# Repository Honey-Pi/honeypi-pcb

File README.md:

# HoneyPi-PCB Overview

Printed circuit boards (PCB) for the Raspberry Pi to connect various sensors to avoid the use of jumper cables and flying resistors :-).

Three variants are available (0.x, 2.x, 3.x):
## HoneyPi-PCB V0.1 [link](./PCB_V0.1) no further development or maintenance.

## HoneyPi-PCB V2.x [link](./PCB_V2.x) designed for Raspberry Zero, Zero 2. Read the manual first for Raspberry 3 and 4.  
## HoneyPi-PCB V3.x [link](./PCB_V3.x) designed for Raspberry 3, Raspberry 4 and the Zeros.
## Rasperry 5 is not yet supported.
--> HoneyPi-PCB V2.x and V3.x have a different range of functions.  
 
## Sensor extension board HX711 & DS18b20 for HoneyPi-PCB V2.x [link](./PCB_Sensor_Board_2.x_HX711_DS18b20)  

## Sensor extension board BME280/680 for HoneyPi-PCB V2.x [link](./PCB_Sensor_Board_2.x_BME280_680_ATH10_HDC1080)  
## I2C Extender (one set to extend the range) [link](./PCB_I2C_Extender)

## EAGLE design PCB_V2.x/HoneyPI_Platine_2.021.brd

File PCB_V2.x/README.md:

# HoneyPi-PCB 2.0x

Printed circuit board (PCB) for the Raspberry Pi ZERO to connect various sensors.  
Pitch lenght 2.x mm for Grove plugs or similar.  
Pitch lenght 2.54 mm for terminal blocks as an alternative. 
 
- Three differend possible power supplies possible.  

- 5x HX711...  

- 8x DS18b20 + 1x DS18b20 (TO-92 onboard)  

- 2x BME680 / BME280 

- 1x I²C interface (instead of second BME)

- 1x PCF8591

- incl. interface for the WittyPi / Timer Board

Designed for the Raspian Zero and NOT for Raspian Pi 1 to 4  
Feature list and bill of material is still on working.  
## You can find some helpfull instructions (only in German at the moment ) [here](./Bienenwaage_Platine_2.x_D2.07.pdf)

## V2.0x circuit diagram [link](./Schaltplan_2.021-13-8-2022.pdf)
Check out this [blogpost](https://honey-pi.de/neue-platine-v2-fuer-raspberry-zero/) for the Raspberry Zero.

Status: Tested, working.  
This version has been tested and found to be good and released.

You can upload this [gerber file](./HoneyPI_Platine_2.021_2022-08-13.zip) to [this manufactory service](https://jlcpcb.com/quote) to get few PCBs. 5 pieces of this board cost me about 7 € with delivery. 

### Pictures

Users of the board version 2.01: Please use the schematic 2.01.1 [link](./OLD/Schaltplan_2.01.1-21.01.2021.pdf)

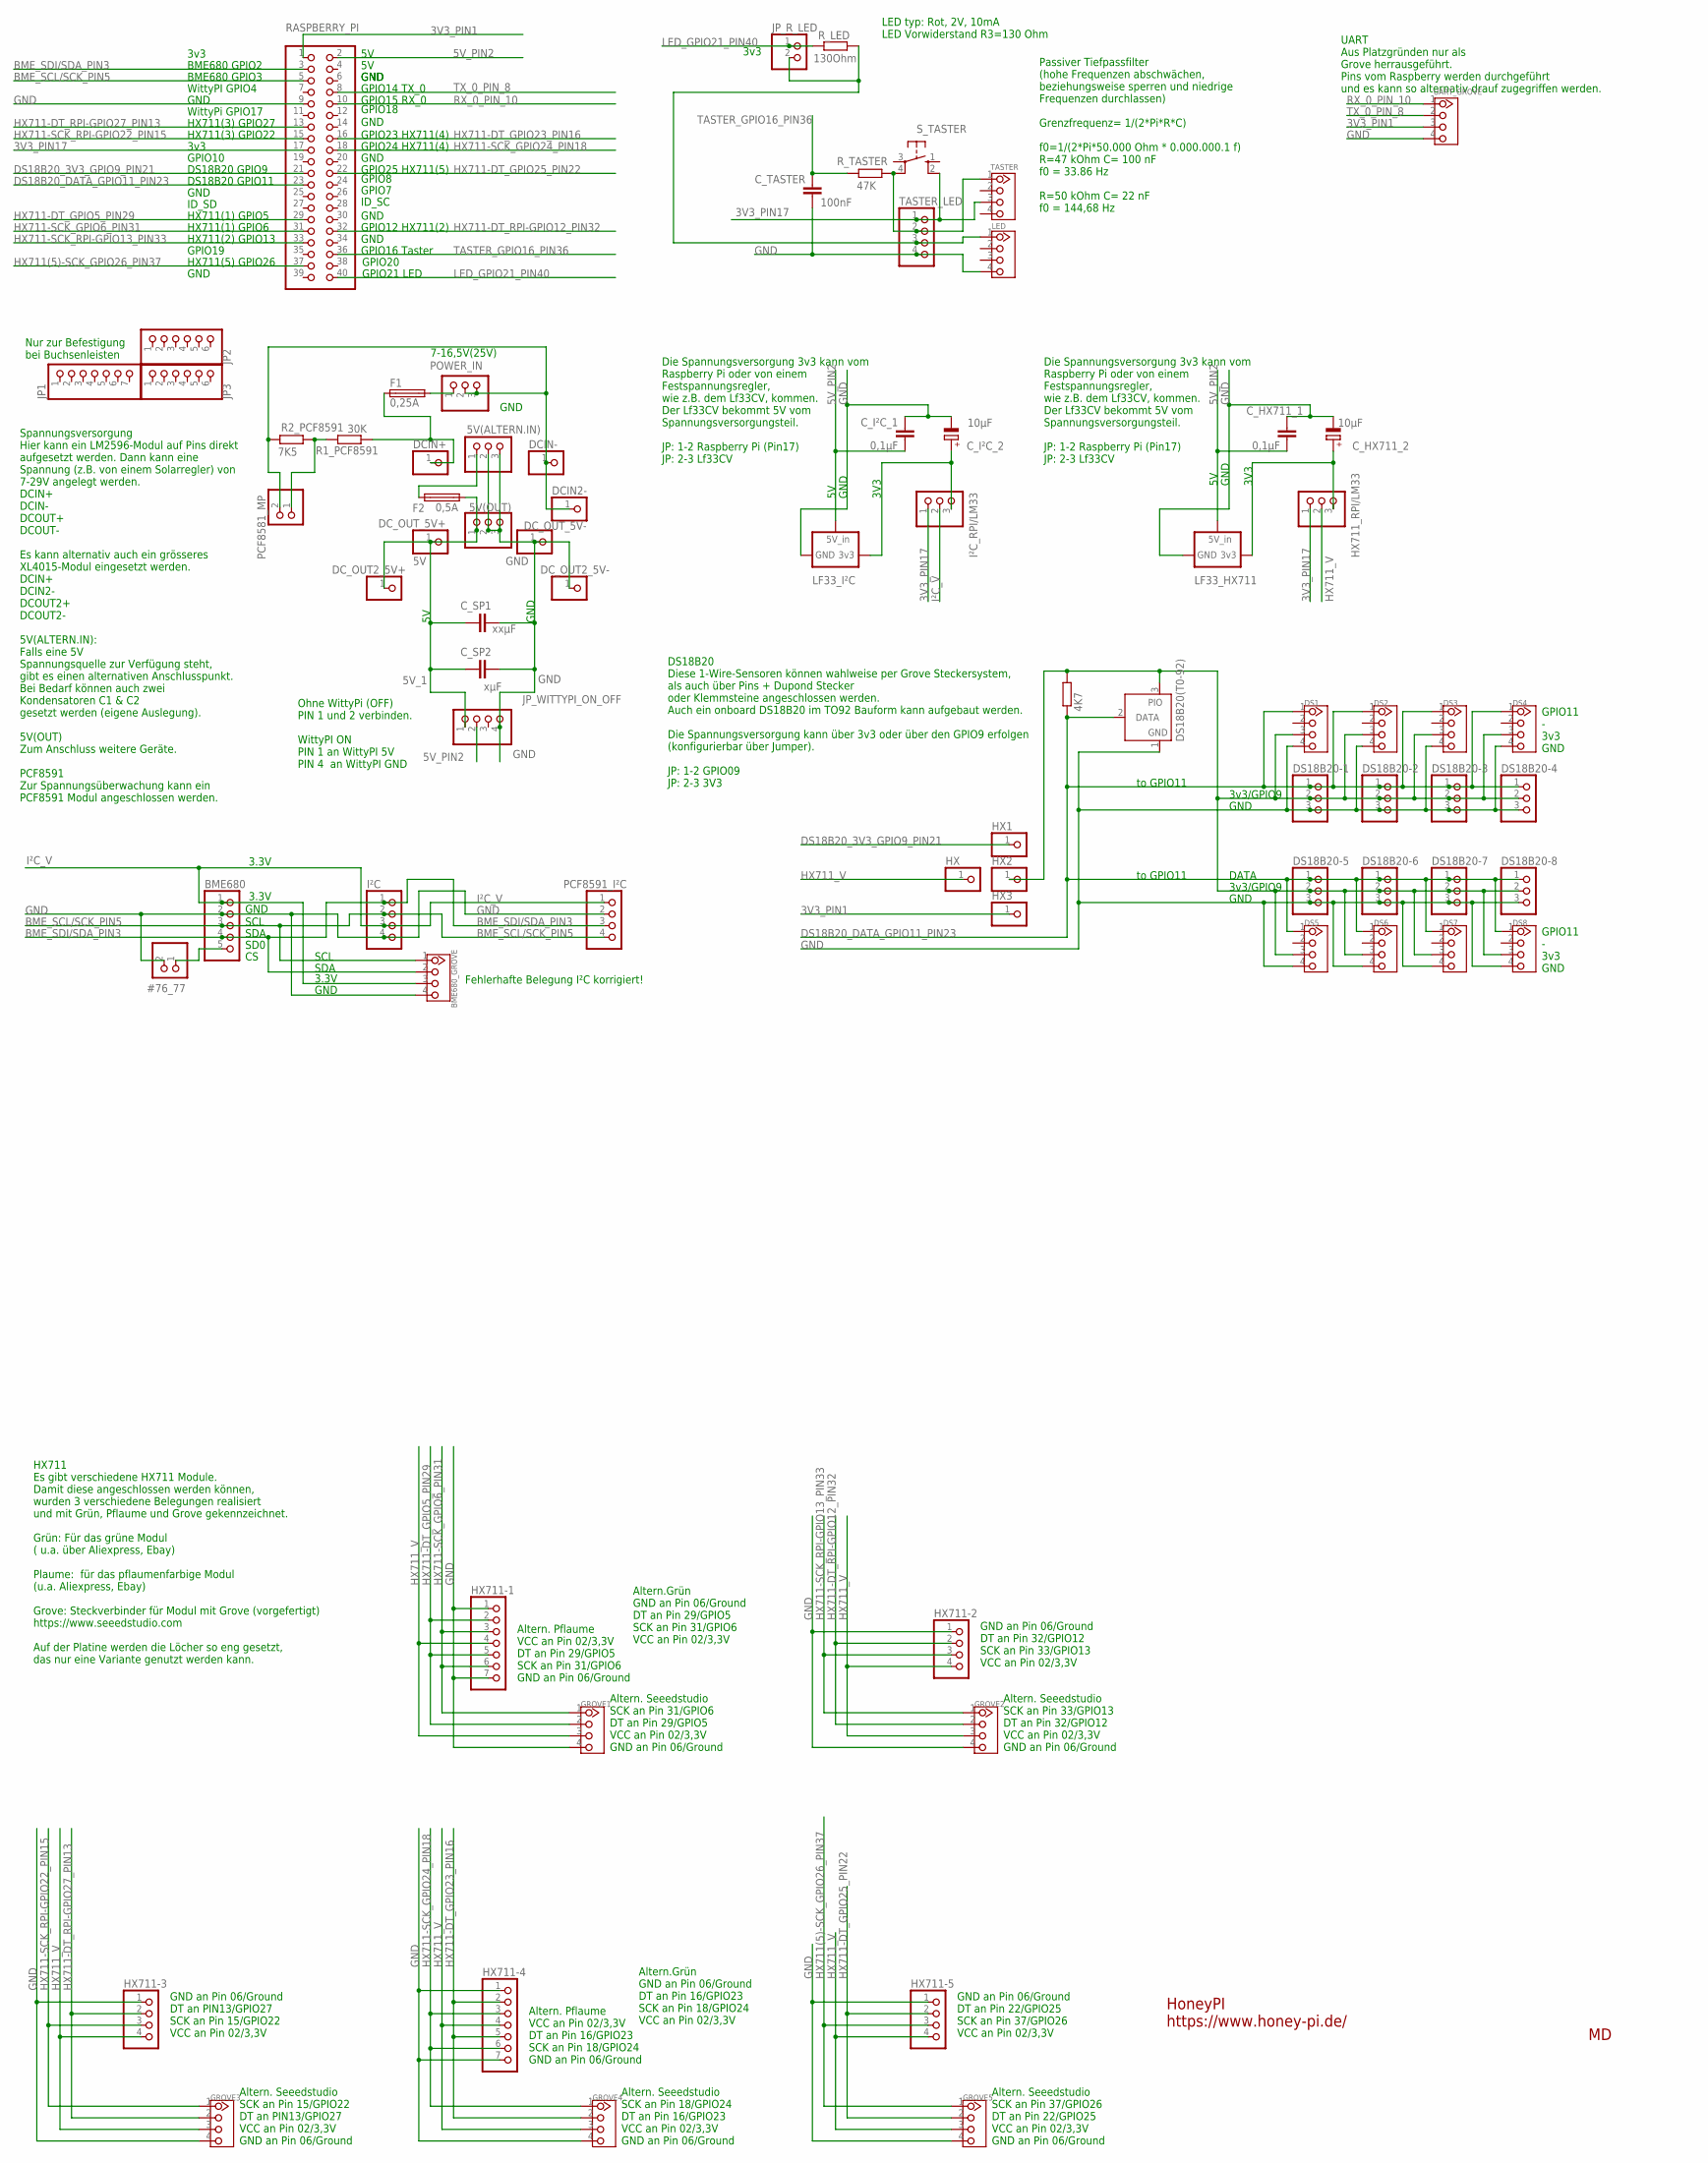
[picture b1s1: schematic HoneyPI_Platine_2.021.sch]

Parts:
5V(ALTERN.IN), 5V(OUT): PINHD-1X3; 1X03
#76_77: PINHD-1X2; 1X02
BME680: PINHD-1X5; 1X05
BME680_GROVE: TWIG-4P-2.0-2.0; 4P-2.0
C_HX711_1: 0,1µF; C2.5-3
C_HX711_2: 10µF; E2-5
C_I²C_1: 0,1µF; C2.5-3
C_I²C_2: 10µF; E2-5
C_SP1: xxµF; C2.5-3
C_SP2: xµF; C2.5-3
C_TASTER: 100nF; C2.5-3
DCIN2-: PINHD-1X1; 1X01
DCIN+: PINHD-1X1; 1X01
DCIN-: PINHD-1X1; 1X01
DC_OUT2_5V+, DC_OUT2_5V-: PINHD-1X1; 1X01
DC_OUT_5V+: 5V; 1X01
DC_OUT_5V-: GND; 1X01
DS1, DS2, DS3, DS4, DS5, DS6, DS7, DS8: TWIG-4P-2.0-2.0; 4P-2.0
DS18B20(T0-92): DS18b20; TO92-
DS18B20-1, DS18B20-2, DS18B20-3, DS18B20-4, DS18B20-5, DS18B20-6, DS18B20-7, DS18B20-8: PINHD-1X3; 1X03
F1: 0,25A; TR5
F2: 0,5A; TR5
GROVE1, GROVE2, GROVE3, GROVE4, GROVE5: TWIG-4P-2.0-2.0; 4P-2.0
HX, HX1, HX2, HX3: PINHD-1X1; 1X01
HX711-1, HX711-4: PINHD-1X7; 1X07
HX711-2, HX711-3, HX711-5: PINHD-1X4; 1X04
HX711_RPI/LM33: PINHD-1X3; 1X03
I²C: PINHD-1X4; 1X04
I²C_RPI/LM33: PINHD-1X3; 1X03
JP1: PINHD-1X7; 1X07
JP2, JP3: PINHD-1X6; 1X06
JP_R_LED: PINHD-1X2; 1X02
JP_WITTYPI_ON_OFF: PINHD-1X4; 1X04
LED: TWIG-4P-2.0-2.0; 4P-2.0
LF33_HX711, LF33_I²C: LM33CV; 337TS
PCF8581_MP: PINHD-1X2; 1X02
PCF8591_I²C: PINHD-1X4; 1X04
POWER_IN: PINHD-1X3; 1X03
R1_PCF8591: 30K; 0204/7
R2_PCF8591: 7K5; 0204/7
RASPBERRY_PI: PINHD-2X20; 2X20
R_DS18B20: 4K7; 0204/7
R_LED: 130Ohm; 0204/7
R_TASTER: 47K; 0204/7
S_TASTER: 10-XX; B3F-10XX
TASTER: TWIG-4P-2.0-2.0; 4P-2.0
TASTER_LED: PINHD-1X4; 1X04
UART_GROVE: TWIG-4P-2.0-2.0; 4P-2.0

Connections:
3V3: DS1.3, DS2.3, DS3.3, DS4.3, DS5.3, DS6.3, DS7.3, DS8.3, DS18B20(T0-92).3 (PIO), DS18B20-1.2, DS18B20-2.2, DS18B20-3.2, DS18B20-4.2, DS18B20-5.2, DS18B20-6.2, DS18B20-7.2, DS18B20-8.2, HX2.1, R_DS18B20.2
3V3_PIN1: HX3.1, RASPBERRY_PI.1, UART_GROVE.3
3V3_PIN17: HX711_RPI/LM33.1, I²C_RPI/LM33.1, RASPBERRY_PI.17, S_TASTER.2 (S1), TASTER.3, TASTER_LED.1
5V_1: 5V(OUT).1, C_SP1.1, C_SP2.1, DC_OUT2_5V+.1, DC_OUT_5V+.1, F2.1, JP_WITTYPI_ON_OFF.1
5V_PIN2: C_HX711_1.1, C_I²C_1.1, JP_WITTYPI_ON_OFF.2, LF33_HX711.1 (5V), LF33_I²C.1 (5V), RASPBERRY_PI.2
BME_SCL/SCK_PIN5: BME680.3, BME680_GROVE.1, I²C.2, PCF8591_I²C.4, RASPBERRY_PI.5
BME_SDI/SDA_PIN3: BME680.4, BME680_GROVE.2, I²C.1, PCF8591_I²C.3, RASPBERRY_PI.3
DS18B20_3V3_GPIO9_PIN21: HX1.1, RASPBERRY_PI.21
DS18B20_DATA_GPIO11_PIN23: DS1.1, DS2.1, DS3.1, DS4.1, DS5.1, DS6.1, DS7.1, DS8.1, DS18B20(T0-92).2 (DATA), DS18B20-1.1, DS18B20-2.1, DS18B20-3.1, DS18B20-4.1, DS18B20-5.1, DS18B20-6.1, DS18B20-7.1, DS18B20-8.1, RASPBERRY_PI.23, R_DS18B20.1
GND: 5V(ALTERN.IN).2, 5V(ALTERN.IN).3, 5V(OUT).2, 5V(OUT).3, #76_77.2, BME680.2, BME680_GROVE.4, C_HX711_1.2, C_HX711_2.-, C_I²C_1.2, C_I²C_2.-, C_SP1.2, C_SP2.2, C_TASTER.1, DC_OUT2_5V-.1, DC_OUT_5V-.1, DS1.4, DS2.4, DS3.4, DS4.4, DS5.4, DS6.4, DS7.4, DS8.4, DS18B20(T0-92).1 (GND), DS18B20-1.3, DS18B20-2.3, DS18B20-3.3, DS18B20-4.3, DS18B20-5.3, DS18B20-6.3, DS18B20-7.3, DS18B20-8.3, GROVE1.4, GROVE2.4, GROVE3.4, GROVE4.4, GROVE5.4, HX711-1.1, HX711-1.7, HX711-2.1, HX711-3.1, HX711-4.1, HX711-4.7, HX711-5.1, I²C.4, JP_WITTYPI_ON_OFF.4, LED.4, LF33_HX711.2 (GND), LF33_I²C.2 (GND), PCF8591_I²C.2, RASPBERRY_PI.9, TASTER_LED.4, UART_GROVE.4
GND20V: DCIN2-.1, DCIN-.1, PCF8581_MP.2, POWER_IN.2, POWER_IN.3, R2_PCF8591.2
HX711(5)-SCK_GPIO26_PIN37: GROVE5.1, HX711-5.3, RASPBERRY_PI.37
HX711-DT_GPIO5_PIN29: GROVE1.2, HX711-1.2, HX711-1.5, RASPBERRY_PI.29
HX711-DT_GPIO23_PIN16: GROVE4.2, HX711-4.2, HX711-4.5, RASPBERRY_PI.16
HX711-DT_GPIO25_PIN22: GROVE5.2, HX711-5.2, RASPBERRY_PI.22
HX711-DT_RPI-GPIO12_PIN32: GROVE2.2, HX711-2.2, RASPBERRY_PI.32
HX711-DT_RPI-GPIO27_PIN13: GROVE3.2, HX711-3.2, RASPBERRY_PI.13
HX711-SCK_GPIO6_PIN31: GROVE1.1, HX711-1.3, HX711-1.6, RASPBERRY_PI.31
HX711-SCK_GPIO24_PIN18: GROVE4.1, HX711-4.3, HX711-4.6, RASPBERRY_PI.18
HX711-SCK_RPI-GPIO13_PIN33: GROVE2.1, HX711-2.3, RASPBERRY_PI.33
HX711-SCK_RPI-GPIO22_PIN15: GROVE3.1, HX711-3.3, RASPBERRY_PI.15
HX711_V: GROVE1.3, GROVE2.3, GROVE3.3, GROVE4.3, GROVE5.3, HX.1, HX711-1.4, HX711-2.4, HX711-3.4, HX711-4.4, HX711-5.4, HX711_RPI/LM33.2
I²C_V: BME680.1, BME680_GROVE.3, I²C.3, I²C_RPI/LM33.2, PCF8591_I²C.1
LED_2: JP_R_LED.2, LED.1, R_LED.2, TASTER_LED.3
LED_GPIO21_PIN40: JP_R_LED.1, RASPBERRY_PI.40, R_LED.1
unnamed: C_I²C_2.+, I²C_RPI/LM33.3, LF33_I²C.3 (OUT3V3)
unnamed: R_TASTER.1, S_TASTER.4 (P1), TASTER.1, TASTER_LED.2
unnamed: C_HX711_2.+, HX711_RPI/LM33.3, LF33_HX711.3 (OUT3V3)
unnamed: #76_77.1, BME680.5
unnamed: 5V(ALTERN.IN).1, F2.2
RX_0_PIN_10: RASPBERRY_PI.10, UART_GROVE.1
SPANNUNGSTEILER1: PCF8581_MP.1, R1_PCF8591.2, R2_PCF8591.1
TASTER_GPIO16_PIN36: C_TASTER.2, RASPBERRY_PI.36, R_TASTER.2
TX_0_PIN_8: RASPBERRY_PI.8, UART_GROVE.2
VDD20V1: DCIN+.1, F1.1, R1_PCF8591.1
VDD20V2: F1.2, POWER_IN.1

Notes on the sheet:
3v3
3v3/GPIO9
DATA
GND
SCL
SDA
SD0
7-16,5V(25V)
Altern. Pflaume VCC an Pin 02/3,3V DT an Pin 29/GPIO5 SCK an Pin 31/GPIO6 GND an Pin 06/Ground
GPIO18
Altern.Grün GND an Pin 06/Ground DT an Pin 29/GPIO5 SCK an Pin 31/GPIO6 VCC an Pin 02/3,3V
BME680 GPIO2
BME680 GPIO3
WittyPI GPIO4
WittyPi GPIO17
DS18B20 GPIO9
DS18B20 GPIO11
HX711(1) GPIO5
HX711(1) GPIO6
HX711(2) GPIO13
GPIO16 Taster
GPIO21 LED
GPIO12 HX711(2)
to GPIO11
GPIO11 - 3v3 GND
GPIO23 HX711(4)
GPIO24 HX711(4)
GPIO25 HX711(5)
HX711(5) GPIO26
GPIO15 RX_0
GPIO14 TX_0
HX711(3) GPIO27
HX711(3) GPIO22
Altern. Seeedstudio SCK an Pin 31/GPIO6 DT an Pin 29/GPIO5 VCC an Pin 02/3,3V GND an Pin 06/Ground
GND an Pin 06/Ground DT an Pin 32/GPIO12 SCK an Pin 33/GPIO13 VCC an Pin 02/3,3V
Altern. Seeedstudio SCK an Pin 33/GPIO13 DT an Pin 32/GPIO12 VCC an Pin 02/3,3V GND an Pin 06/Ground
GND an Pin 06/Ground DT an PIN13/GPIO27 SCK an Pin 15/GPIO22 VCC an Pin 02/3,3V
Altern. Seeedstudio SCK an Pin 15/GPIO22 DT an PIN13/GPIO27 VCC an Pin 02/3,3V GND an Pin 06/Ground
Altern. Pflaume VCC an Pin 02/3,3V DT an Pin 16/GPIO23 SCK an Pin 18/GPIO24 GND an Pin 06/Ground
Altern.Grün GND an Pin 06/Ground DT an Pin 16/GPIO23 SCK an Pin 18/GPIO24 VCC an Pin 02/3,3V

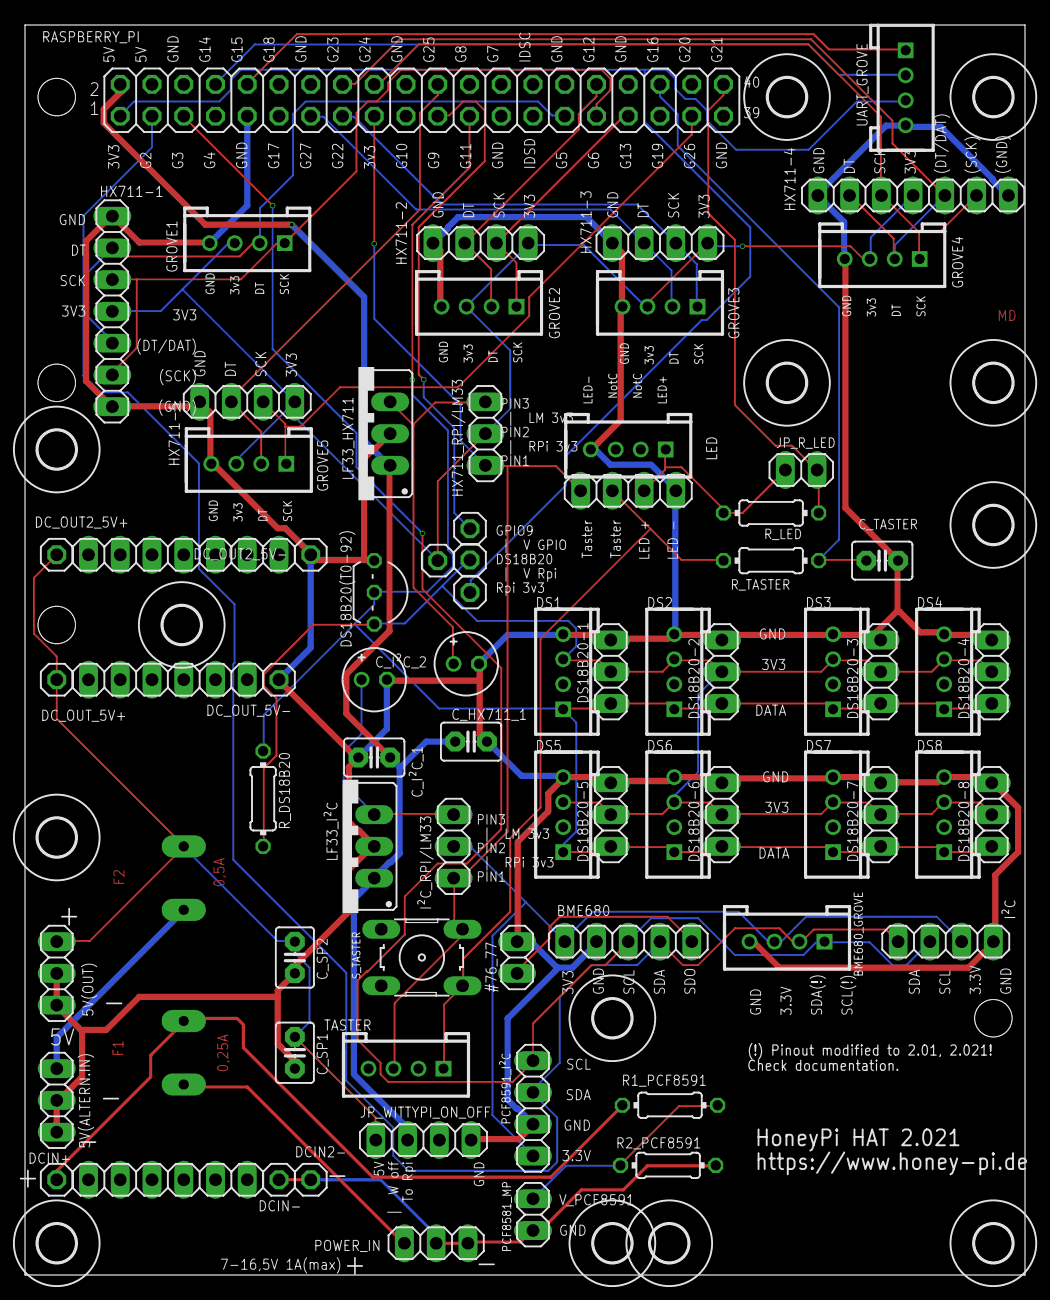
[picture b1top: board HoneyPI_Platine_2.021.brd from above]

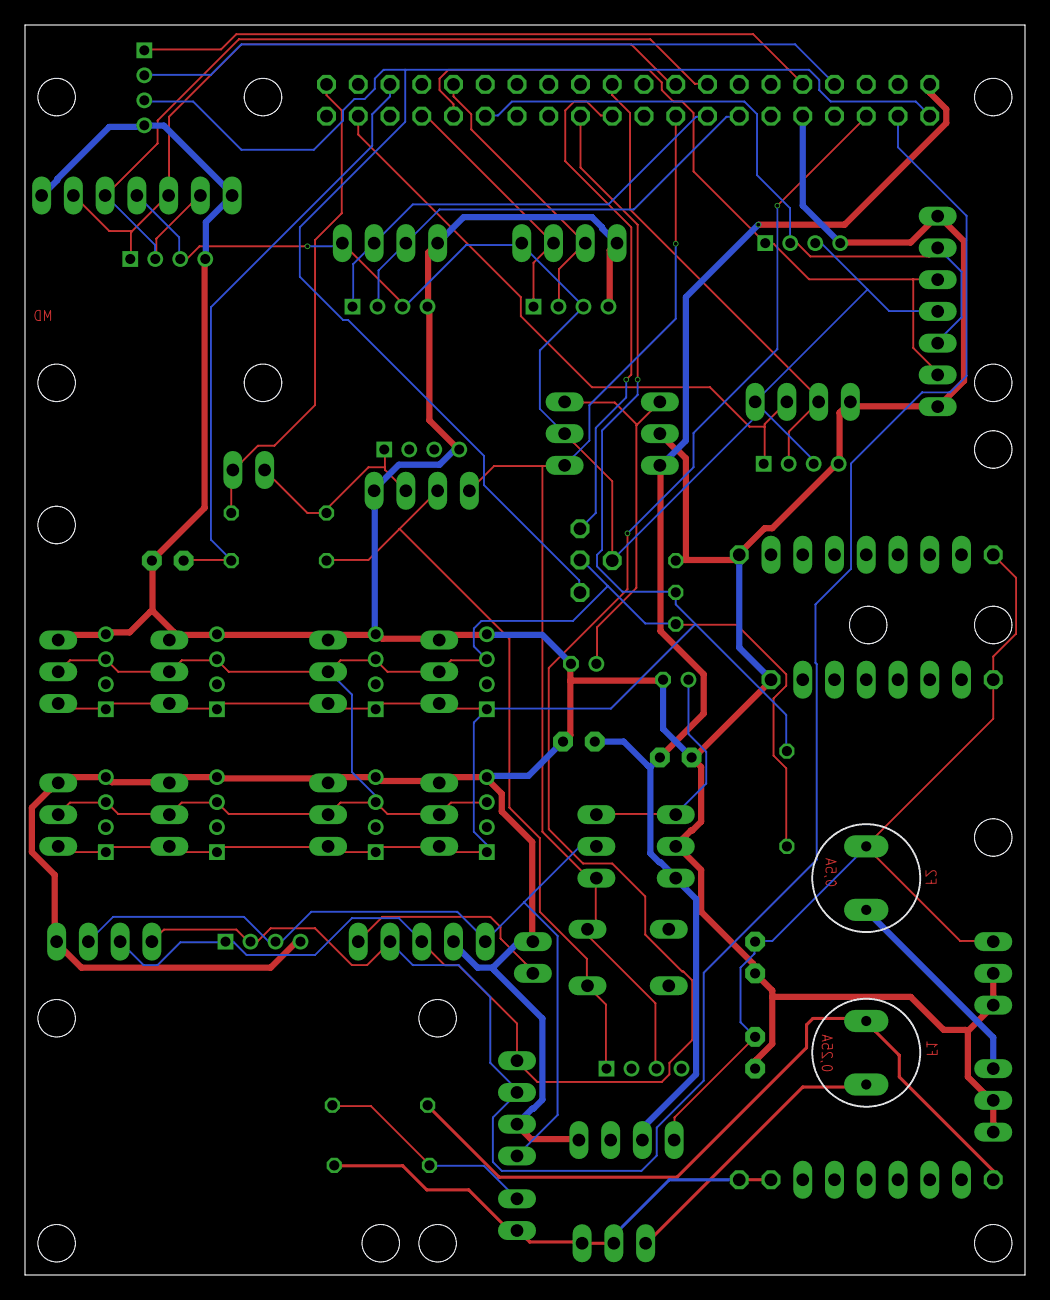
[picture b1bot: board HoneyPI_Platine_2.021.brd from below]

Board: 2 copper layers, 80.0 x 100.0 mm, 89 parts (2 on the bottom side), 36 nets.

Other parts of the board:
U$1, U$2, U$3, U$4, U$5, U$6, U$7, U$8, U$9, U$10, U$11, U$12, U$13: 3,0

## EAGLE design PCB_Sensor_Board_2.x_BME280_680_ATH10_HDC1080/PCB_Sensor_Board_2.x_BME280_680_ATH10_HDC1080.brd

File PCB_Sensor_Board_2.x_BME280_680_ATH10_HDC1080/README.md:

# HoneyPI-PCB Sensor Board 2.x BME280/BME680

Extension board for the HoneyPi-PCB 2.x.  
Pitch lenght 2.0 mm for Grove plugs or similar.  
Pitch lenght 2.54 mm for pins or...  
Designed to be mounted in a separate housing that allows humidity to be measured.  
1x BME680 or BME280 or 1x ATH10 or 1x HDC1080 or 1x sht31
--> We adapt these sensors because of the fixed i2c adresses. 

Feature list and bill of material is still on working.   

## V2.0x circuit diagram [link](./PCB_Sensor_Board_2.x_BME280_680_ATH10_HDC1080.pdf)
Check out this [blogpost](https://www.honey-pi.de/)

Status: Under development.  
This version is currently being procured and tested.  
Please do not order these without having contacted us before.  
Thank you for your understanding!  

You can upload this [gerber file](./PCB_Sensor_Board_2.x_BME280_680_ATH10_HDC1080.zip) to [this manufactory service](https://jlcpcb.com/quote) to get few PCBs. 10 pieces of this board cost about 7 € with delivery. 

### Pictures

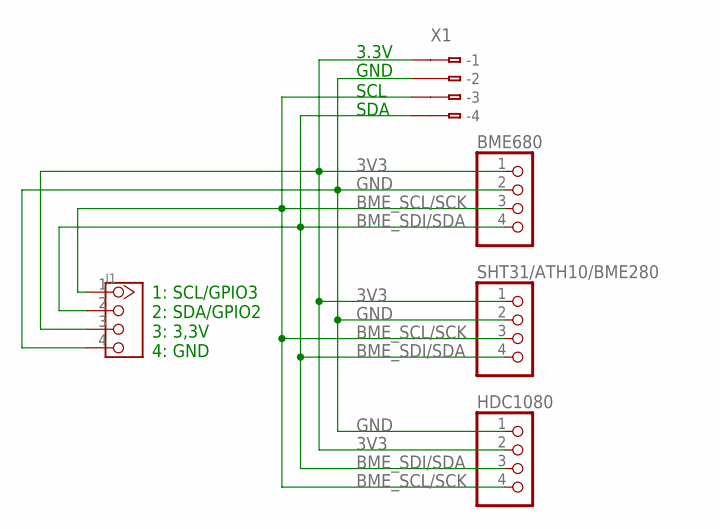
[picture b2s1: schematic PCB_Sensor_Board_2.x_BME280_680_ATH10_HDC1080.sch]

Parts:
BME680: PINHD-1X4; 1X04
HDC1080: PINHD-1X4; 1X04
J1: TWIG-4P-2.0-2.0; 4P-2.0
SHT31/ATH10/BME280: PINHD-1X4; 1X04
X1: 233-504

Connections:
3V3: BME680.1, HDC1080.2, J1.3, SHT31/ATH10/BME280.1, X1.B1 (B-1)
BME_SCL/SCK: BME680.3, HDC1080.4, J1.1, SHT31/ATH10/BME280.3, X1.B3 (B-3)
BME_SDI/SDA: BME680.4, HDC1080.3, J1.2, SHT31/ATH10/BME280.4, X1.B4 (B-4)
GND: BME680.2, HDC1080.1, J1.4, SHT31/ATH10/BME280.2, X1.B2 (B-2)

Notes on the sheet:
GND
SDA
SCL
3.3V
1: SCL/GPIO3 2: SDA/GPIO2 3: 3,3V 4: GND

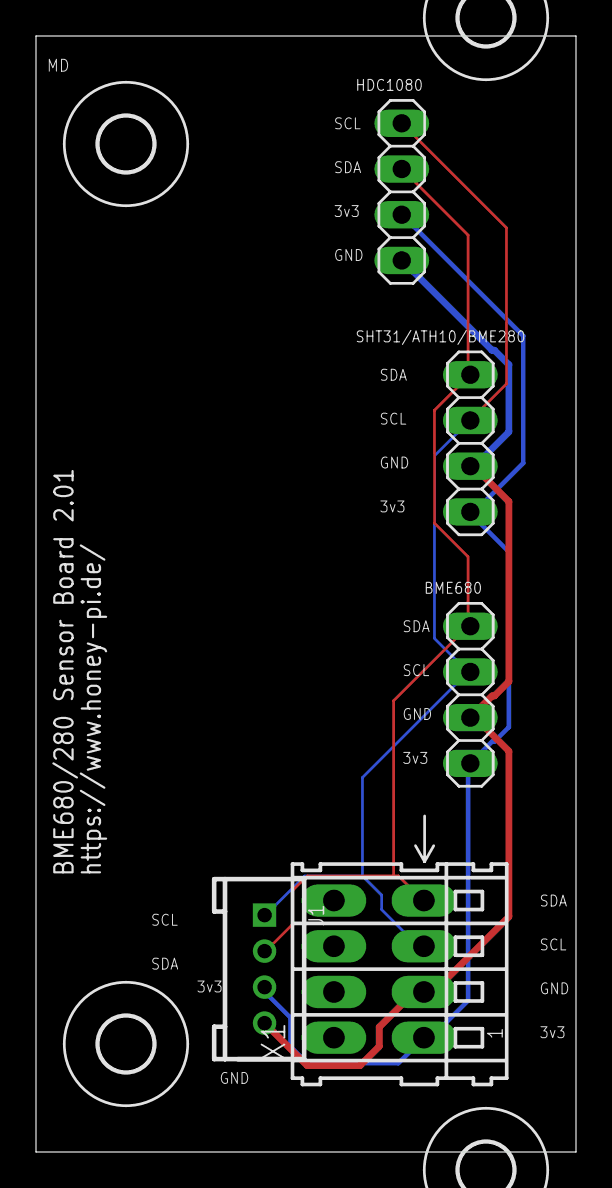
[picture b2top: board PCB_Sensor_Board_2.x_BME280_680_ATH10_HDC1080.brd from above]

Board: 2 copper layers, 30.0 x 62.0 mm, 9 parts (0 on the bottom side), 4 nets.

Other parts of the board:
U$1, U$2, U$3, U$4: 3,0

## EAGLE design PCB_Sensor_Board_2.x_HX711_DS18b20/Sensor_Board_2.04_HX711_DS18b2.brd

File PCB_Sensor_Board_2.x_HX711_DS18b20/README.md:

# HoneyPi-PCB Sensor Board HX711 and DS18b20

Extension board for the HoneyPi-PCB 2.x.   
Pitch lenght 2.0 mm for Grove plugs or similar.  
Pitch lenght 2.54 mm for (e.g.) terminal blocks as an alternative. 
New: Wago cage clamp block support

Designed to be mounted close to the load cell. To ensure that the analogue voltage signal is subject to the least interference.  
Shielded cable to the load cell and aluminium housing are designed for this purpose.  
1x HX711 (two different types)  
3x DS18b20 (cable/external) + 1x DS18b20 TO-92 (board)  

Feature list and bill of material is still on working. 

## V2.0x circuit diagram [link](./HoneyPI_Platine_2.05_Sensor_Plan.pdf)  
Check out this [blogpost](https://www.honey-pi.de/)  

Status: Under development.  
This version is currently being procured and tested.  
Please do not order these without having contacted us before.  
Thank you for your understanding!   

You can upload this [gerber file](./Sensor_Board_2.05_HX711_DS18b2.zip) to [this manufactory service](https://jlcpcb.com/quote) to get few PCBs. 10 pieces of this board cost about 7 € with delivery.  
(price date 2021)

### Pictures

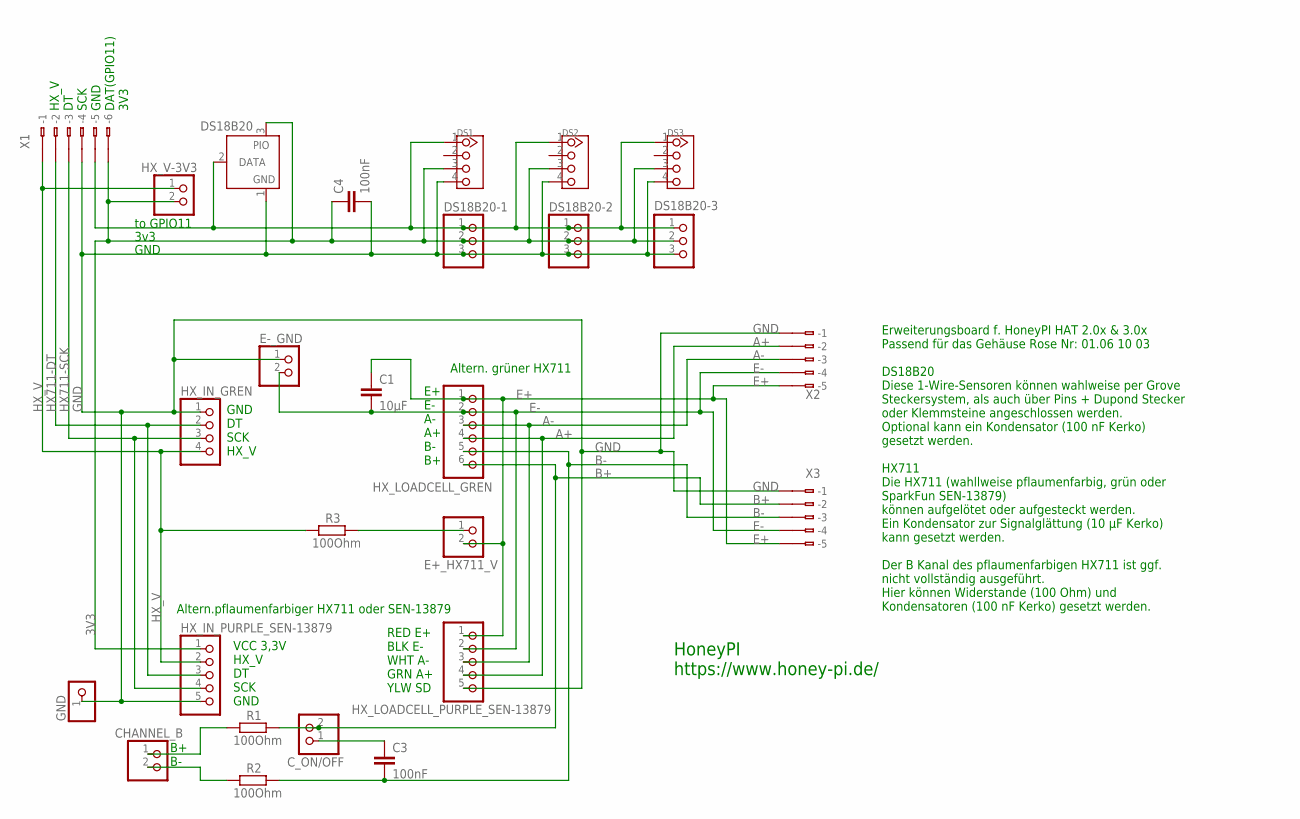
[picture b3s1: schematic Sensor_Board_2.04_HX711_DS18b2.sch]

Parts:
C1: 10µF; C5B2.5
C3, C4: 100nF; C5B2.5
CHANNEL_B: PINHD-1X2; 1X02
C_ON/OFF: PINHD-1X2; 1X02
DS1, DS2, DS3: TWIG-4P-2.0-2.0; 4P-2.0
DS18B20: DS2405; TO92-
DS18B20-1, DS18B20-2, DS18B20-3: PINHD-1X3; 1X03
E+_HX711_V: PINHD-1X2; 1X02
E-_GND: PINHD-1X2; 1X02
GND: PINHD-1X1; 1X01
HX_IN_GREN: PINHD-1X4; 1X04
HX_IN_PURPLE_SEN-13879: PINHD-1X5; 1X05
HX_LOADCELL_GREN: PINHD-1X6; 1X06
HX_LOADCELL_PURPLE_SEN-13879: PINHD-1X5; 1X05
HX_V-3V3: PINHD-1X2; 1X02
R1, R2, R3: 100Ohm; 0207/10
X1: 233-506
X2, X3: 233-505

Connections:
3V3: C4.1, DS1.3, DS2.3, DS3.3, DS18B20.3 (PIO), DS18B20-1.2, DS18B20-2.2, DS18B20-3.2, HX_IN_PURPLE_SEN-13879.1, HX_V-3V3.2, X1.B6 (B-6)
A+: HX_LOADCELL_GREN.4, HX_LOADCELL_PURPLE_SEN-13879.4, X2.B2 (B-2)
A-: HX_LOADCELL_GREN.3, HX_LOADCELL_PURPLE_SEN-13879.3, X2.B3 (B-3)
B+: C_ON/OFF.2, HX_LOADCELL_GREN.6, R1.2, X3.B2 (B-2)
B-: C3.2, HX_LOADCELL_GREN.5, R2.2, X3.B3 (B-3)
DS18B20_DATA_GPIO11_PIN23: DS1.1, DS2.1, DS3.1, DS18B20.2 (DATA), DS18B20-1.1, DS18B20-2.1, DS18B20-3.1, X1.B5 (B-5)
E+: C1.1, E+_HX711_V.2, HX_LOADCELL_GREN.1, HX_LOADCELL_PURPLE_SEN-13879.1, X2.B5 (B-5), X3.B5 (B-5)
E-: C1.2, E-_GND.2, HX_LOADCELL_GREN.2, HX_LOADCELL_PURPLE_SEN-13879.2, X2.B4 (B-4), X3.B4 (B-4)
GND: C4.2, DS1.4, DS2.4, DS3.4, DS18B20.1 (GND), DS18B20-1.3, DS18B20-2.3, DS18B20-3.3, E-_GND.1, GND.1, HX_IN_GREN.1, HX_IN_PURPLE_SEN-13879.5, HX_LOADCELL_PURPLE_SEN-13879.5, X1.B4 (B-4), X2.B1 (B-1), X3.B1 (B-1)
HX711-DT: HX_IN_GREN.2, HX_IN_PURPLE_SEN-13879.3, X1.B2 (B-2)
HX711-SCK: HX_IN_GREN.3, HX_IN_PURPLE_SEN-13879.4, X1.B3 (B-3)
HX_V: HX_IN_GREN.4, HX_IN_PURPLE_SEN-13879.2, HX_V-3V3.1, R3.1, X1.B1 (B-1)
unnamed: CHANNEL_B.1, R1.1
unnamed: CHANNEL_B.2, R2.1
unnamed: C3.1, C_ON/OFF.1
unnamed: E+_HX711_V.1, R3.2

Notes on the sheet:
3v3
VCC 3,3V HX_V DT SCK GND
GND DT SCK HX_V
GND
to GPIO11
Erweiterungsboard f. HoneyPI HAT 2.0x & 3.0x Passend für das Gehäuse Rose Nr: 01.06 10 03 DS18B20 Diese 1-Wire-Sensoren können wahlweise per Grove Steckersystem, als auch über Pins + Dupond Stecker oder Klemmsteine angeschlossen werden. Optional kann ein Kondensator (100 nF Kerko) gesetzt werden. H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
E+ E- A- A+ B- B+
RED E+ BLK E- WHT A- GRN A+ YLW SD
B+ B-
Altern.pflaumenfarbiger HX711 oder SEN-13879
Altern. grüner HX711
HX_V DT SCK GND DAT(GPIO11) 3V3
HoneyPI https://www.honey-pi.de/

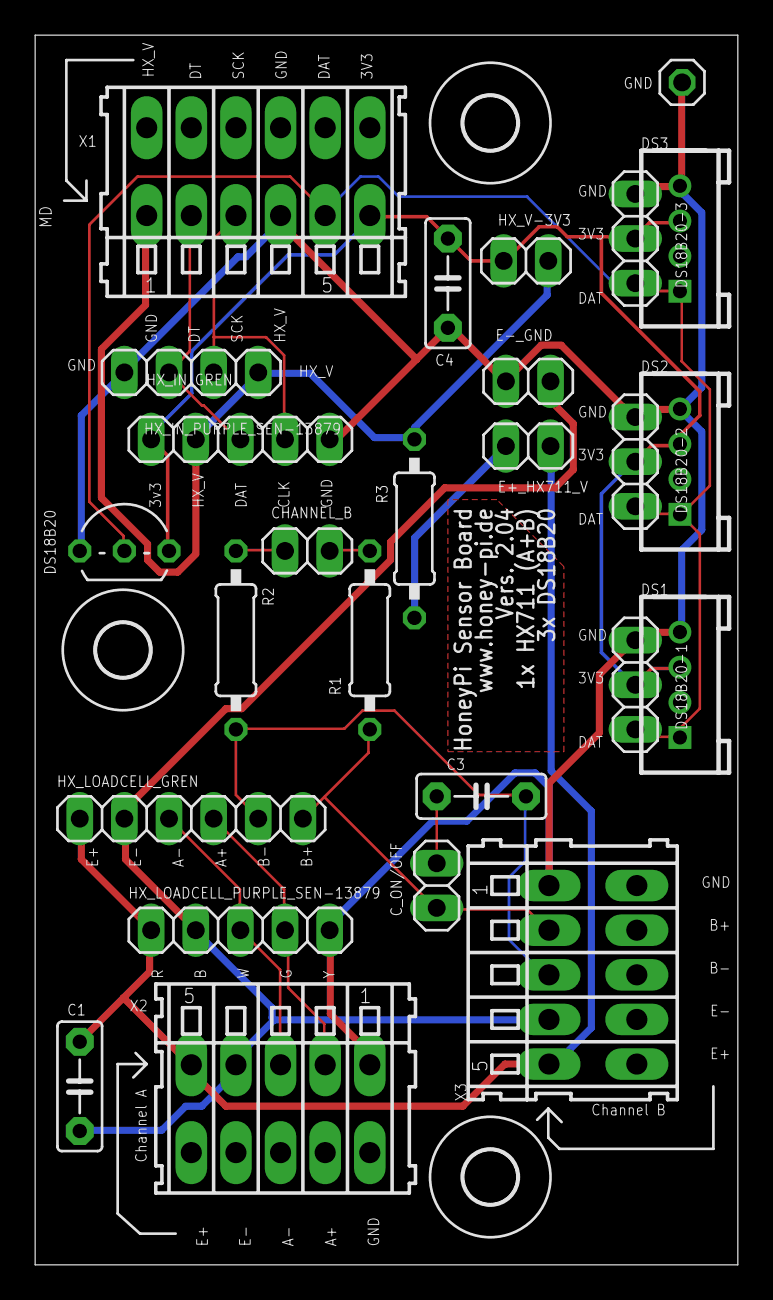
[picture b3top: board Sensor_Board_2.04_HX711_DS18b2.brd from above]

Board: 2 copper layers, 40.0 x 70.0 mm, 29 parts (0 on the bottom side), 16 nets.

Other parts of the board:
U$1, U$2, U$5: 3,0

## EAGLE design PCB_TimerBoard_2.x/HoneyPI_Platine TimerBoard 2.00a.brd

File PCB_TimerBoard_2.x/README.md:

# HoneyPI-PCB TimerBoard 2.x

Extension board for the HoneyPi-PCB 2.x.  
Pitch lenght 2.54 mm for pins or...  
Designed to be mounted on a Raspberry Pi Zero

Feature list and bill of material is still on working.   

## V2.0 circuit diagram [link](./HoneyPI_Platine_TimerBoard_2.0.pdf)
Check out this [blogpost](https://www.honey-pi.de/)

Status: 

  Hardware: Release candidate.
  
  Software: under development.  
  
This Hardware version is procured and tested.  

You can upload this [gerber file](./HoneyPI_Platine_TimerBoard_2.00a_2020-12-19.zip) to [this manufactory service](https://jlcpcb.com/quote) to get few PCBs. 10 pieces of this board cost about 7 € with delivery. 

### Pictures

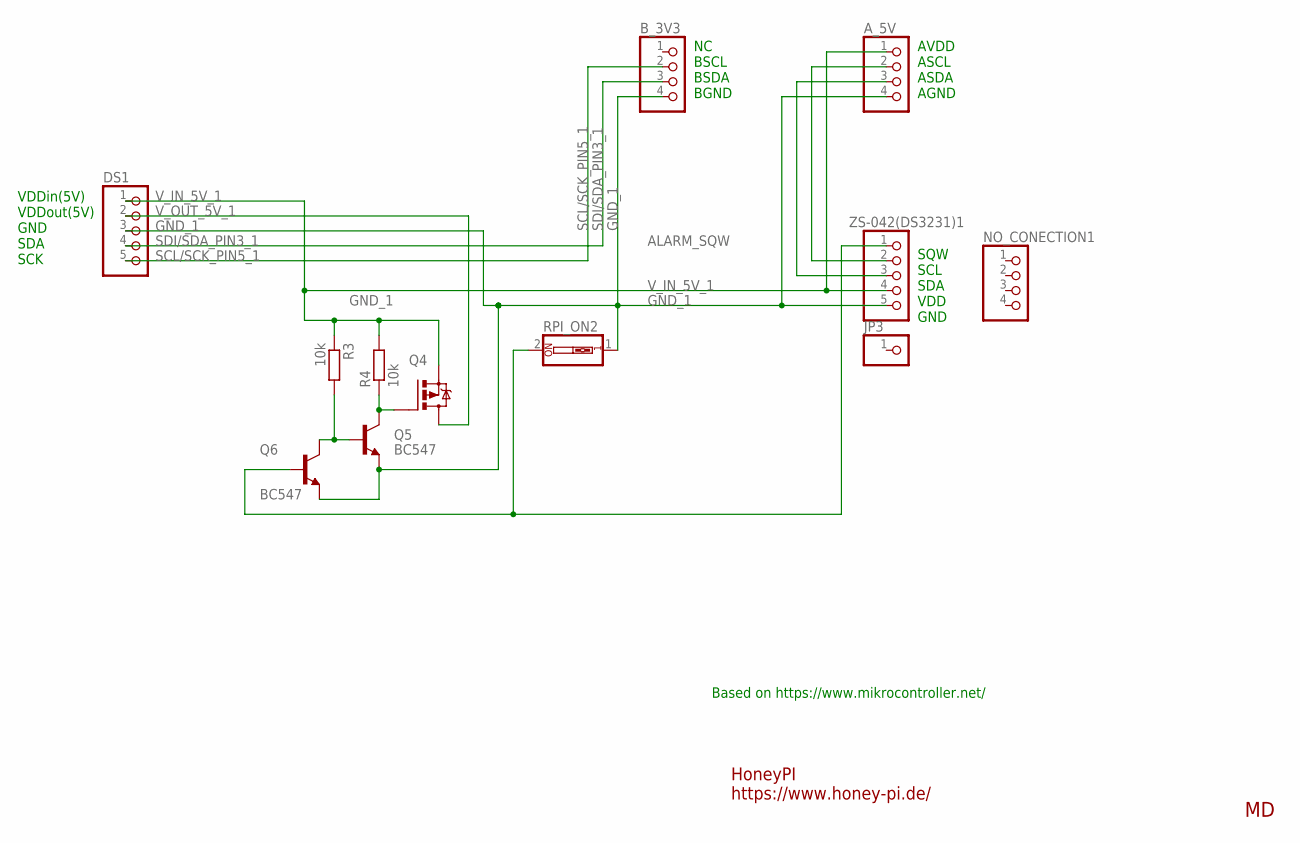
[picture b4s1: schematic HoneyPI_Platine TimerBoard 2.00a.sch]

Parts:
A_5V: PINHD-1X4; 1X04
B_3V3: PINHD-1X4; 1X04
DS1: PINHD-1X5; 1X05
JP3: PINHD-1X1; 1X01
NO_CONECTION1: PINHD-1X4; 1X04
Q4: NDP6020P; TO220BV
Q5, Q6: BC547; TO92-EBC
R3, R4: 10k; 0204/7
RPI_ON2: SW_DIP-1; EDG-01
ZS-042(DS3231)1: PINHD-1X5; 1X05

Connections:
ALARM_SQW: Q6.B, RPI_ON2.2, ZS-042(DS3231)1.1
GND_1: A_5V.4, B_3V3.4, DS1.3, Q5.E, Q6.E, RPI_ON2.1, ZS-042(DS3231)1.5
unnamed: Q4.G, Q5.C, R4.1
unnamed: Q5.B, Q6.C, R3.2
unnamed: A_5V.3, ZS-042(DS3231)1.3
unnamed: A_5V.2, ZS-042(DS3231)1.2
SCL/SCK_PIN5_1: B_3V3.2, DS1.5
SDI/SDA_PIN3_1: B_3V3.3, DS1.4
V_IN_5V_1: A_5V.1, DS1.1, Q4.S, R3.1, R4.2, ZS-042(DS3231)1.4
V_OUT_5V_1: DS1.2, Q4.D

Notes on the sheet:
HoneyPI https://www.honey-pi.de/
Based on https://www.mikrocontroller.net/
SQW SCL SDA VDD GND
VDDin(5V) VDDout(5V) GND SDA SCK
AVDD ASCL ASDA AGND
NC BSCL BSDA BGND

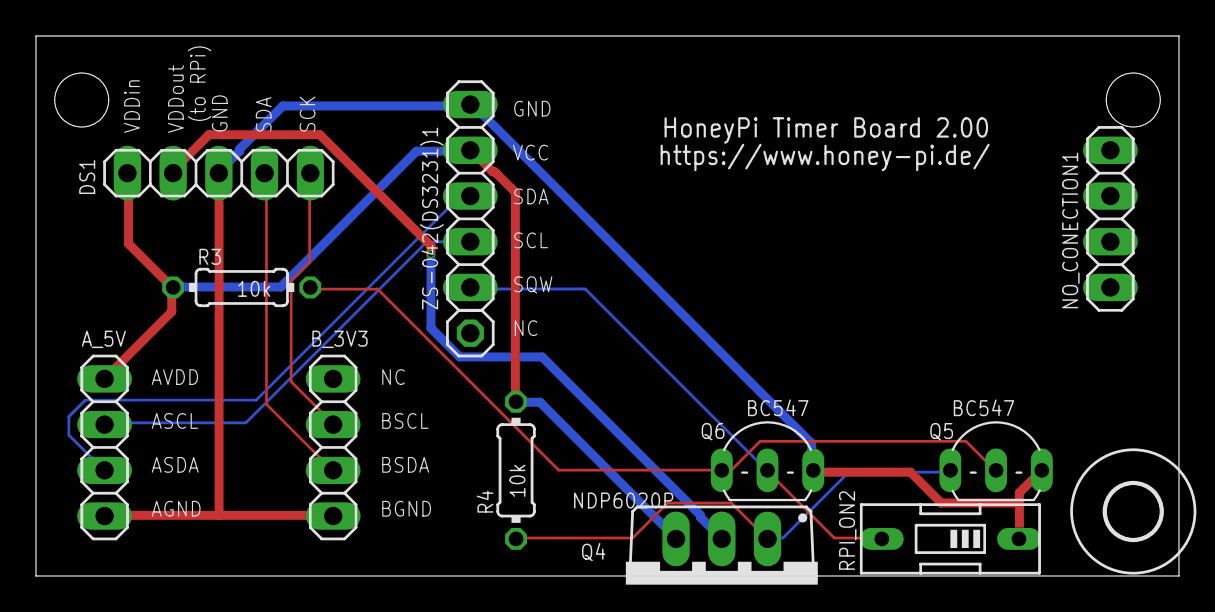
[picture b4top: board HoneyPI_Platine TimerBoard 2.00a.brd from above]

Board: 2 copper layers, 63.5 x 30.0 mm, 13 parts (0 on the bottom side), 10 nets.

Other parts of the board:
U$1: 3,0

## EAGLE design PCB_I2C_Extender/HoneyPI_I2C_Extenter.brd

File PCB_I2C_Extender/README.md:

# HoneyPI-PCB I2C_Extenter

Extension board for the HoneyPi-PCB 2.x.  
Pitch lenght 2.54 mm for pins or...  
Designed to be connect to a Raspberry Pi on the I²C

(-> Two modules on one board, so a saw is needed)

Feature list and bill of material is still on working.   

## V2.0 BETA circuit diagram [link](./HoneyPI_I2C_Extenter.pdf)
Check out this [blogpost](https://www.honey-pi.de/)

Status: Under development.  
This version is currently being procured and tested.  
Please do not order these without having contacted us before.  
Thank you for your understanding!  

NOT YET: You can upload this [gerber file](./HoneyPI_I2C_Extenter_2020-12-14.zip) to [this manufactory service](https://jlcpcb.com/quote) to get few PCBs. 10 pieces of this board cost about 7 € with delivery. 

### Pictures

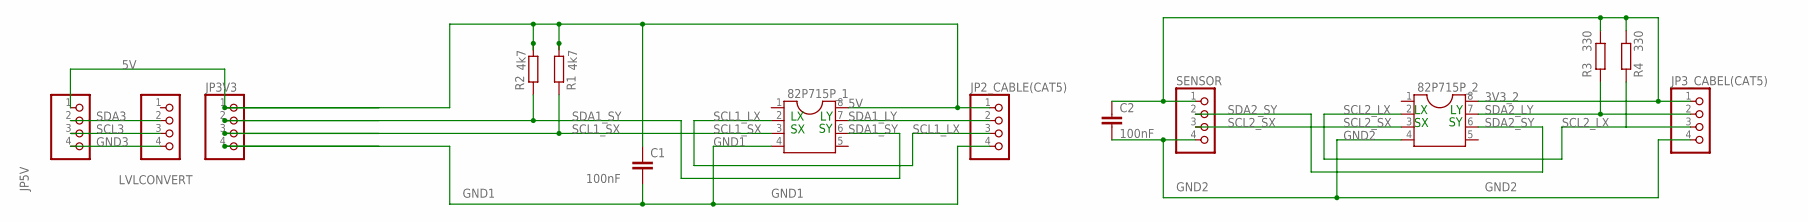
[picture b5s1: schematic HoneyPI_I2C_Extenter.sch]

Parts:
82P715P_1, 82P715P_2: DIL8; DIL08
C1, C2: 100nF; C050-045X075
JP2_CABLE(CAT5), JP3V3, JP3_CABEL(CAT5), JP5V: PINHD-1X4; 1X04
LVLCONVERT: PINHD-1X4; 1X04
R1, R2: 4k7; 0207/7
R3, R4: 330; 0207/7
SENSOR: PINHD-1X4; 1X04

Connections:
3V3_2: 82P715P_2.8, C2.1, JP3_CABEL(CAT5).1, R3.1, R4.1, SENSOR.1
5V: 82P715P_1.8, C1.1, JP2_CABLE(CAT5).1, JP3V3.1, JP5V.1, R1.1, R2.1
GND1: 82P715P_1.4, C1.2, JP2_CABLE(CAT5).4, JP3V3.4
GND2: 82P715P_2.4, C2.2, JP3_CABEL(CAT5).4, SENSOR.4
GND3: JP5V.4, LVLCONVERT.4
SCL1_LX: 82P715P_1.2, JP2_CABLE(CAT5).3
SCL1_SX: 82P715P_1.3, JP3V3.3, R1.2
SCL2_LX: 82P715P_2.2, JP3_CABEL(CAT5).3, R4.2
SCL2_SX: 82P715P_2.3, SENSOR.3
SCL3: JP5V.3, LVLCONVERT.3
SDA1_LY: 82P715P_1.7, JP2_CABLE(CAT5).2
SDA1_SY: 82P715P_1.6, JP3V3.2, R2.2
SDA2_LY: 82P715P_2.7, JP3_CABEL(CAT5).2, R3.2
SDA2_SY: 82P715P_2.6, SENSOR.2
SDA3: JP5V.2, LVLCONVERT.2

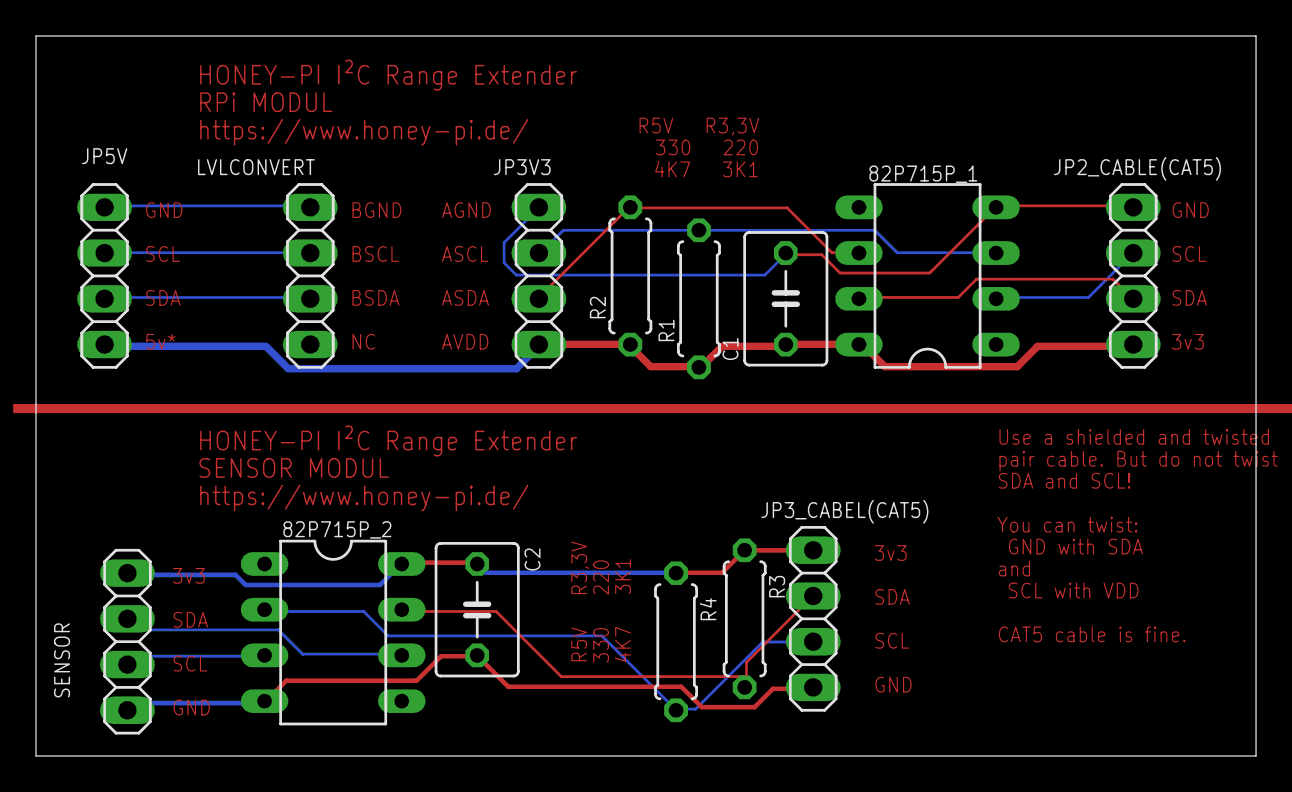
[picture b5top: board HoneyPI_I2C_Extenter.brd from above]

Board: 2 copper layers, 67.8 x 40.0 mm, 14 parts (0 on the bottom side), 15 nets.

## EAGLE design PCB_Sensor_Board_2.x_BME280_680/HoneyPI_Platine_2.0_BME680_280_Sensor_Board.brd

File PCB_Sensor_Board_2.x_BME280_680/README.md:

# HoneyPI-PCB Sensor Board 2.x BME280/BME680

Extension board for the HoneyPi-PCB 2.x.  
Pitch lenght 2.0 mm for Grove plugs or similar.  
Pitch lenght 2.54 mm for pins or...  
Designed to be mounted in a separate housing that allows humidity to be measured.  
1x BME680 (or BME280)  
2x I²C   
...we are am thinking about a sunlight sensor or.

Feature list and bill of material is still on working.   

## V2.0 BETA circuit diagram [link](./HoneyPI_Platine_2.0_BME680_280_Sensor_Board_21-8-2020.pdf)
Check out this [blogpost](https://www.honey-pi.de/)

Status: Under development.  
This version is currently being procured and tested.  
Please do not order these without having contacted us before.  
Thank you for your understanding!  

You can upload this [gerber file](./HoneyPI_Platine_2.0_BME680_280_Sensor_Board_2020-08-21.zip) to [this manufactory service](https://jlcpcb.com/quote) to get few PCBs. 10 pieces of this board cost about 7 € with delivery. 

### Pictures

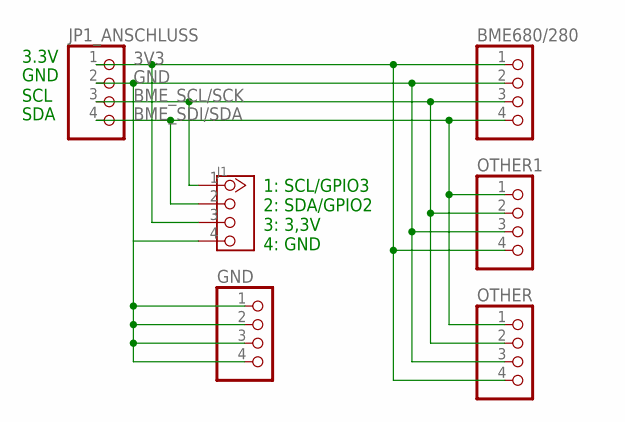
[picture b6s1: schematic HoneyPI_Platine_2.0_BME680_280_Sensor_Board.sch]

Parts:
BME680/280: PINHD-1X4; 1X04
GND: PINHD-1X4; 1X04
J1: TWIG-4P-2.0-2.0; 4P-2.0
JP1_ANSCHLUSS: PINHD-1X4; 1X04
OTHER, OTHER1: PINHD-1X4; 1X04

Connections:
3V3: BME680/280.1, J1.3, JP1_ANSCHLUSS.1, OTHER.4, OTHER1.4
BME_SCL/SCK: BME680/280.3, J1.1, JP1_ANSCHLUSS.3, OTHER.2, OTHER1.2
BME_SDI/SDA: BME680/280.4, J1.2, JP1_ANSCHLUSS.4, OTHER.1, OTHER1.1
GND: BME680/280.2, GND.1, GND.2, GND.3, GND.4, J1.4, JP1_ANSCHLUSS.2, OTHER.3, OTHER1.3

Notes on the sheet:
GND
SDA
SCL
3.3V
1: SCL/GPIO3 2: SDA/GPIO2 3: 3,3V 4: GND
